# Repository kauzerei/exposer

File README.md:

# Exposer

Exposure timer for PCB production. 
Can be also used for screen printing or other analog printing techniques.
Quickly knocked together using parts I had laying around.

Pictures are of a previous generation.

## Parts list

TODO: write down particular parts used

- Arduino Nano
- ULN2003 or similar darlington transistor array
- TM1637 4 Digit 7-Segment LED
- 18650 cell with leads or 18650 holder
- Encoder with button
- Switch
- UV LED strip

## Dependency

TM1637Display library is used for driving seven-segment display.
It's the one that comes with Arduino IDE.

https://github.com/avishorp/TM1637

## PCB

The board is one-sided to allow easy fabrication at home.
KiCad project is in ```exposer_pcb```.
Neagtive artwork is in PDF format, but it's better to open the KiCad project for soldering.

## Assembly

3d-print every model once, except the legs, you need four of them.
Put the LED-strips into holding pockets, solder them together and to longer power-in cable.  
Fix the legs with 4mm screws or however you like.
Assemble the PCB.
Don't forget to set the correct voltage on boost converter.
Connect the LEDs to the board and you are ready to go.

## Customizing

You can change the 3d-model even if you don't really know OpenSCAD language.
OpenSCAD has customizer module, in which you can graphically change the parameters.
You can use longer LED strips or more of them.

## Usage

Rotating the encoder changes exposure in relative EV units.
Display shows time in seconds, or denominator of a fraction of a second.
It ```:``` symbol is present on display, it's fraction, if not - whole seconds.
Every step divides or multiplies the exposure time.
Pressing the encoder starts exposure and shows countdown.

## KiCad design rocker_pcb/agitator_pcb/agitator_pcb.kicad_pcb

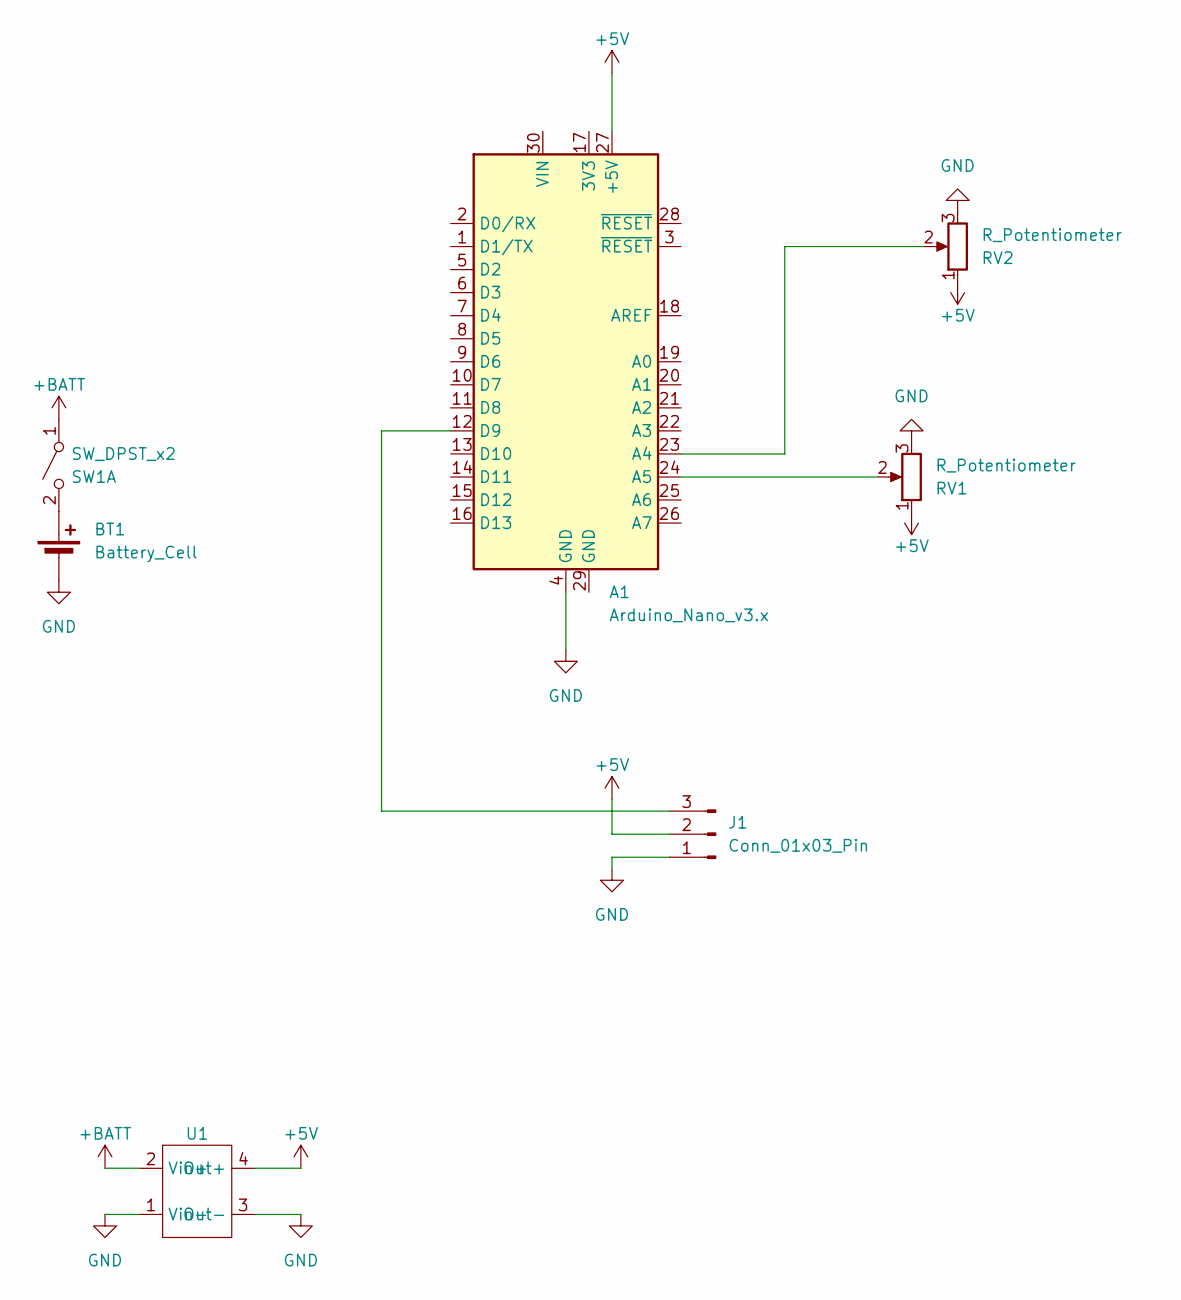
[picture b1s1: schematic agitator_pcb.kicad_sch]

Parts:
A1: Arduino_Nano_v3.x; Arduino_Nano
BT1: Battery_Cell; BatteryHolder_MPD_BH-18650-PC
J1: Conn_01x03_Pin; PinHeader_1x03_P2.54mm_Vertical
RV1, RV2: R_Potentiometer; Potentiometer_Piher_T-16H_Single_Horizontal
SW1: SW_DPST_x2; PinSocket_1x02_P2.54mm_Vertical
U1: dc-dc module

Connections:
+5V: A1.27 (+5V), J1.2, RV1.1, RV2.1, U1.4 (Out+)
+BATT: SW1.1 (A), U1.2 (Vin+)
GND: A1.4 (GND), BT1.2 (-), J1.1, RV1.3, RV2.3, U1.1 (Vin-), U1.3 (Out-)
unnamed: A1.23 (A4), RV2.2
unnamed: A1.24 (A5), RV1.2
unnamed: A1.12 (D9), J1.3
unnamed: BT1.1 (+), SW1.2 (B)

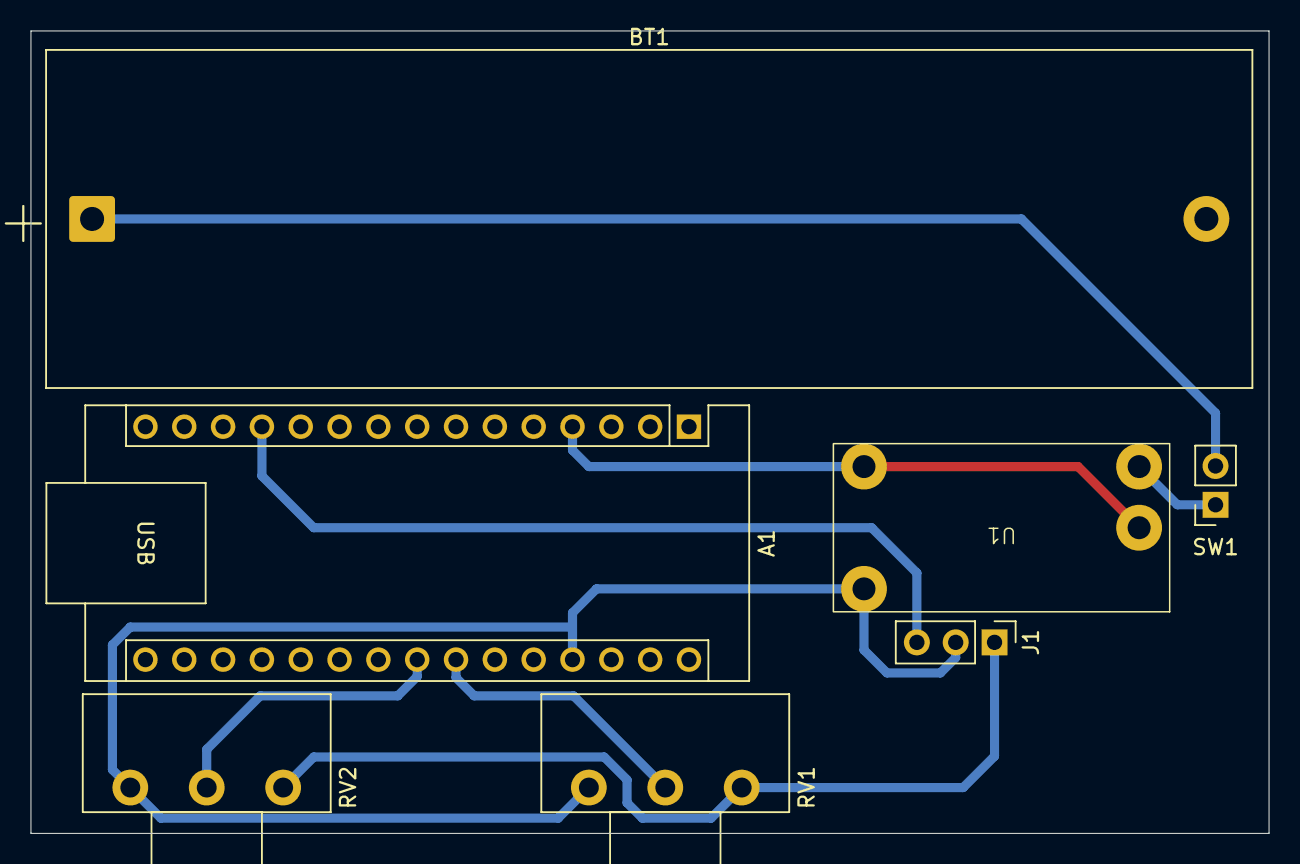
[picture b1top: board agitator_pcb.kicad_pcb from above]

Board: 2 copper layers, 81.0 x 52.5 mm, 7 parts (0 on the bottom side), 7 nets.

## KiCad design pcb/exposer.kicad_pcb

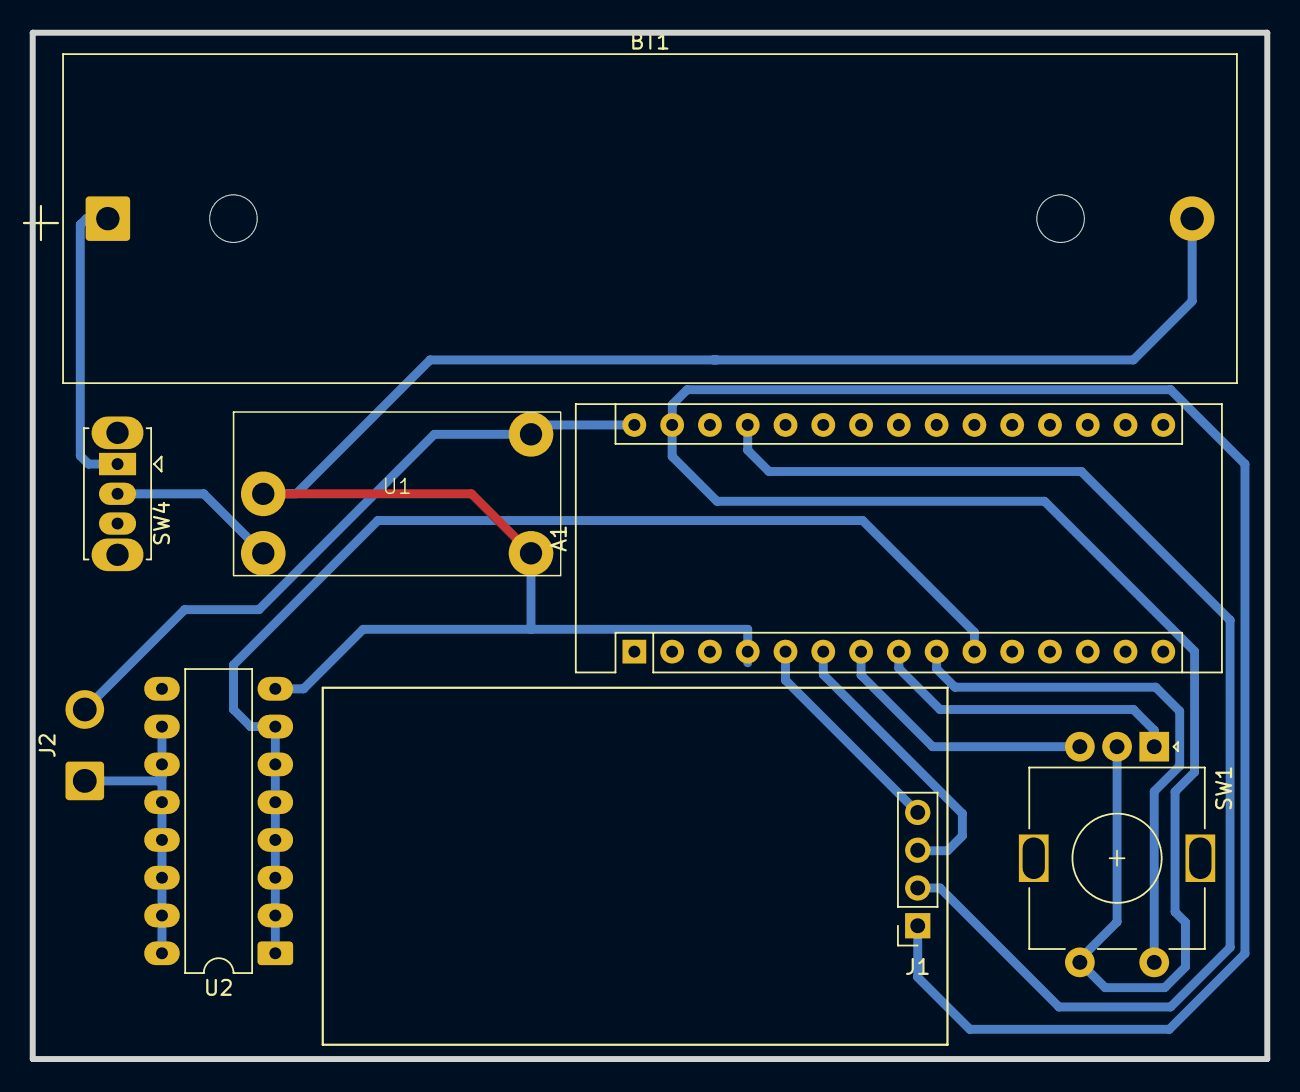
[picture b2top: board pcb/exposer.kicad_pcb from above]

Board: 2 copper layers, 83.0 x 69.0 mm, 8 parts (0 on the bottom side), 12 nets.

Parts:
A1: Arduino_Nano_v3.x; Arduino_Nano
BT1: Battery_Cell; BatteryHolder_MPD_BH-18650-PC
J1: Conn_01x04_Female; PinSocket_1x04_P2.54mm_Vertical
J2: Conn_01x02; SolderWire-0.75sqmm_1x02_P4.8mm_D1.25mm_OD2.3mm
SW1: RotaryEncoder_Switch; RotaryEncoder_Alps_EC11E-Switch_Vertical_H20mm
SW4: SW_SPST; SW_Slide_SPDT_Straight_CK_OS102011MS2Q
U1: dc-dc module
U2: ULN2003A; DIP-16_W7.62mm_LongPads

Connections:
+5V: A1.27 (+5V), J1.2
+12V: A1.30 (VIN), J2.2, U1.4 (Out+)
+BATT: SW4.2 (B), U1.2 (Vin+)
GND: A1.4 (GND), A1.29 (GND), BT1.2 (-), J1.1, SW1.C, SW1.S1, U1.1 (Vin-), U1.3 (Out-), U2.8 (GND)
unnamed: A1.5 (D2), J1.4
unnamed: A1.6 (D3), J1.3
unnamed: A1.7 (D4), SW1.B
unnamed: A1.8 (D5), SW1.A
unnamed: A1.9 (D6), SW1.S2
unnamed: A1.10 (D7), U2.1 (I1), U2.2 (I2), U2.3 (I3), U2.4 (I4), U2.5 (I5), U2.6 (I6), U2.7 (I7)
unnamed: BT1.1 (+), SW4.1 (A)
unnamed: J2.1, U2.10 (O7), U2.11 (O6), U2.12 (O5), U2.13 (O4), U2.14 (O3), U2.15 (O2), U2.16 (O1)

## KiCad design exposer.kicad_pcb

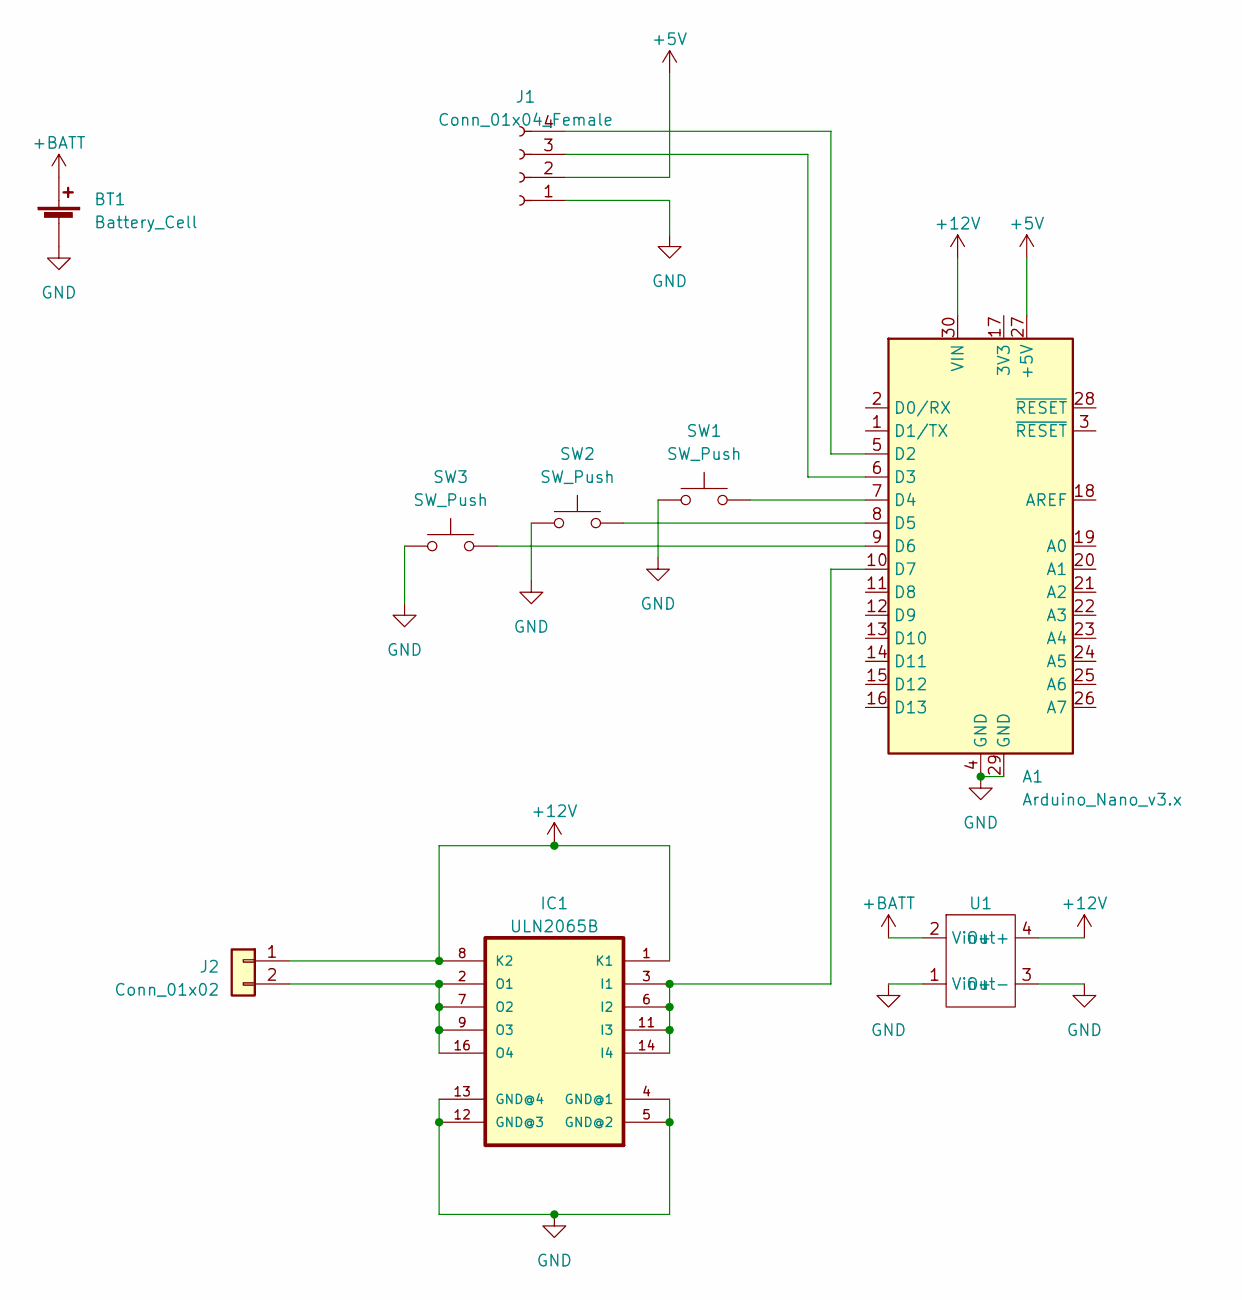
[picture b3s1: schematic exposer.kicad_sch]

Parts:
A1: Arduino_Nano_v3.x; Arduino_Nano
BT1: Battery_Cell; BatteryHolder_Keystone_1042_1x18650
IC1: ULN2065B; DIP-16_W7.62mm_LongPads
J1: Conn_01x04_Female; PinSocket_1x04_P2.54mm_Vertical
J2: Conn_01x02; SolderWirePad_1x02_P7.62mm_Drill2mm
SW1, SW2, SW3: SW_Push; SW_PUSH_6mm_H5mm
U1: dc-dc module

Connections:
+5V: A1.27 (+5V), J1.2
+12V: A1.30 (VIN), IC1.1 (K1), IC1.8 (K2), J2.1, U1.4 (Out+)
+BATT: BT1.1 (+), U1.2 (Vin+)
GND: A1.4 (GND), A1.29 (GND), BT1.2 (-), IC1.4 (GND@1), IC1.5 (GND@2), IC1.12 (GND@3), IC1.13 (GND@4), J1.1, SW1.1, SW2.1, SW3.1, U1.1 (Vin+), U1.3 (Out-)
unnamed: A1.5 (D2), J1.4
unnamed: A1.6 (D3), J1.3
unnamed: A1.7 (D4), SW1.2
unnamed: A1.8 (D5), SW2.2
unnamed: A1.9 (D6), SW3.2
unnamed: A1.10 (D7), IC1.3 (I1), IC1.6 (I2), IC1.11 (I3), IC1.14 (I4)
unnamed: IC1.2 (O1), IC1.7 (O2), IC1.9 (O3), IC1.16 (O4), J2.2

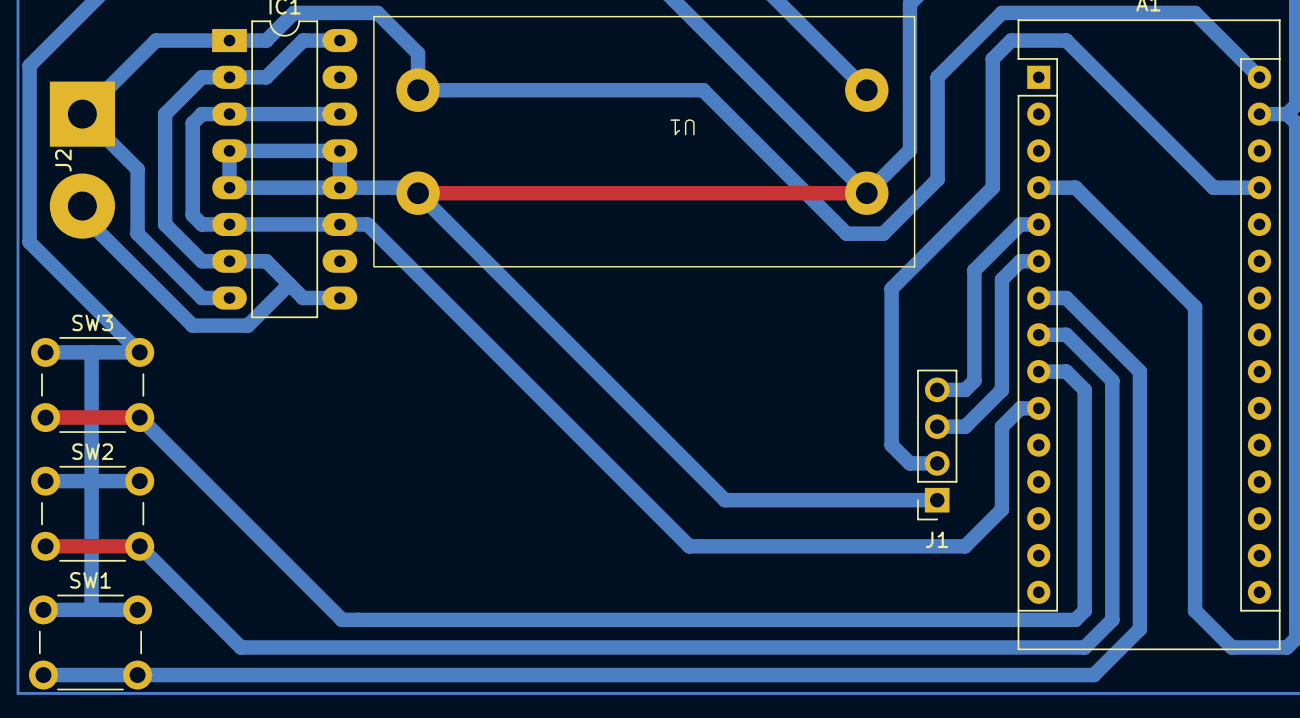
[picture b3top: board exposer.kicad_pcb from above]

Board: 2 copper layers, 9 parts (1 on the bottom side), 11 nets.

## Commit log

2024-04-03 works
2024-05-16 add switch. reorganize
2024-05-16 documentation
2024-05-16 3d printed parts
2024-05-16 clean up kicad backups
2024-05-16 add pictures
2024-05-16 fix comments
2024-05-17 replace pictures
2024-05-17 i thought i could fix the pix with web interface
2025-10-27 yet another exposer
2025-11-03 I guess this branch is just a stash now
2025-11-04 3d model update
2025-11-04 encoder pcb
2025-11-04 screen was upside down
2025-11-04 code works with encoder
2025-11-05 debounce
2025-11-12 agitating thingy
2025-11-13 reorganize
2025-11-13 some more documenting
2025-11-16 model seems fine
2025-11-16 forgot to actually add model lol
2025-11-16 more betterer modl
2025-11-17 model tuning
2025-11-17 cleanup
2025-11-17 pcb optimisation
2025-11-25 more stable mechanics, some fabrication changes
2025-11-28 first adjustable rocker code
2025-12-02 better code
2025-12-02 working tested code
2025-12-03 separated from lab rocker repo
